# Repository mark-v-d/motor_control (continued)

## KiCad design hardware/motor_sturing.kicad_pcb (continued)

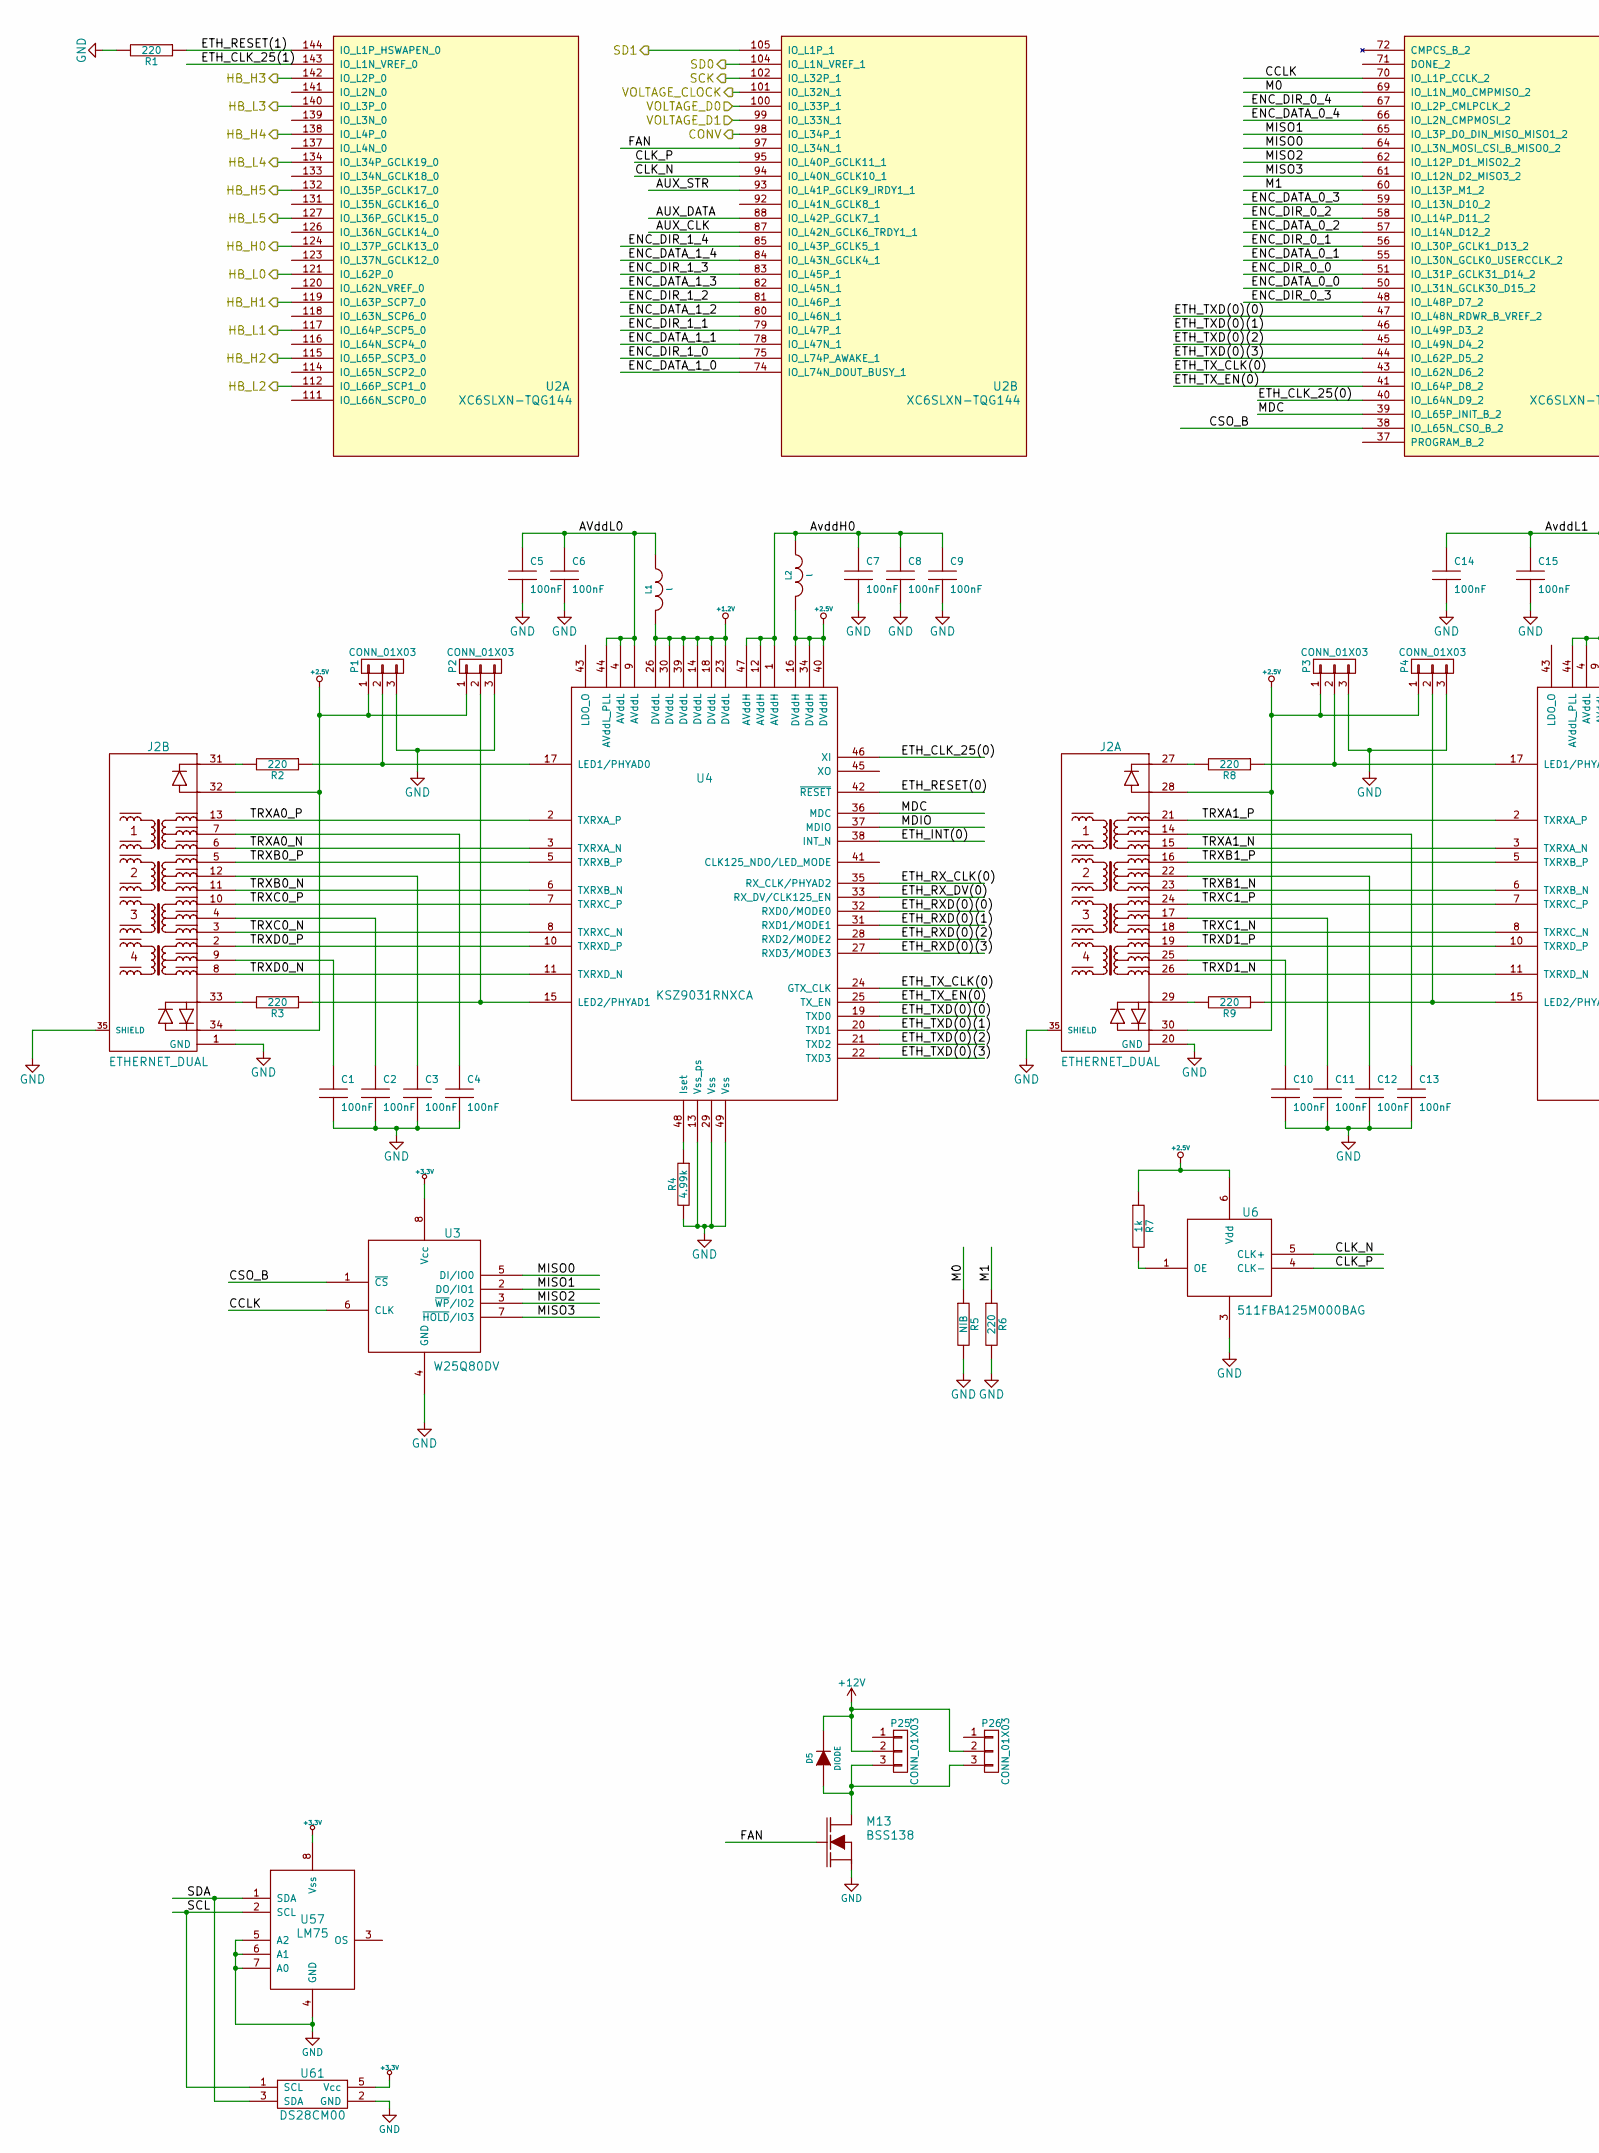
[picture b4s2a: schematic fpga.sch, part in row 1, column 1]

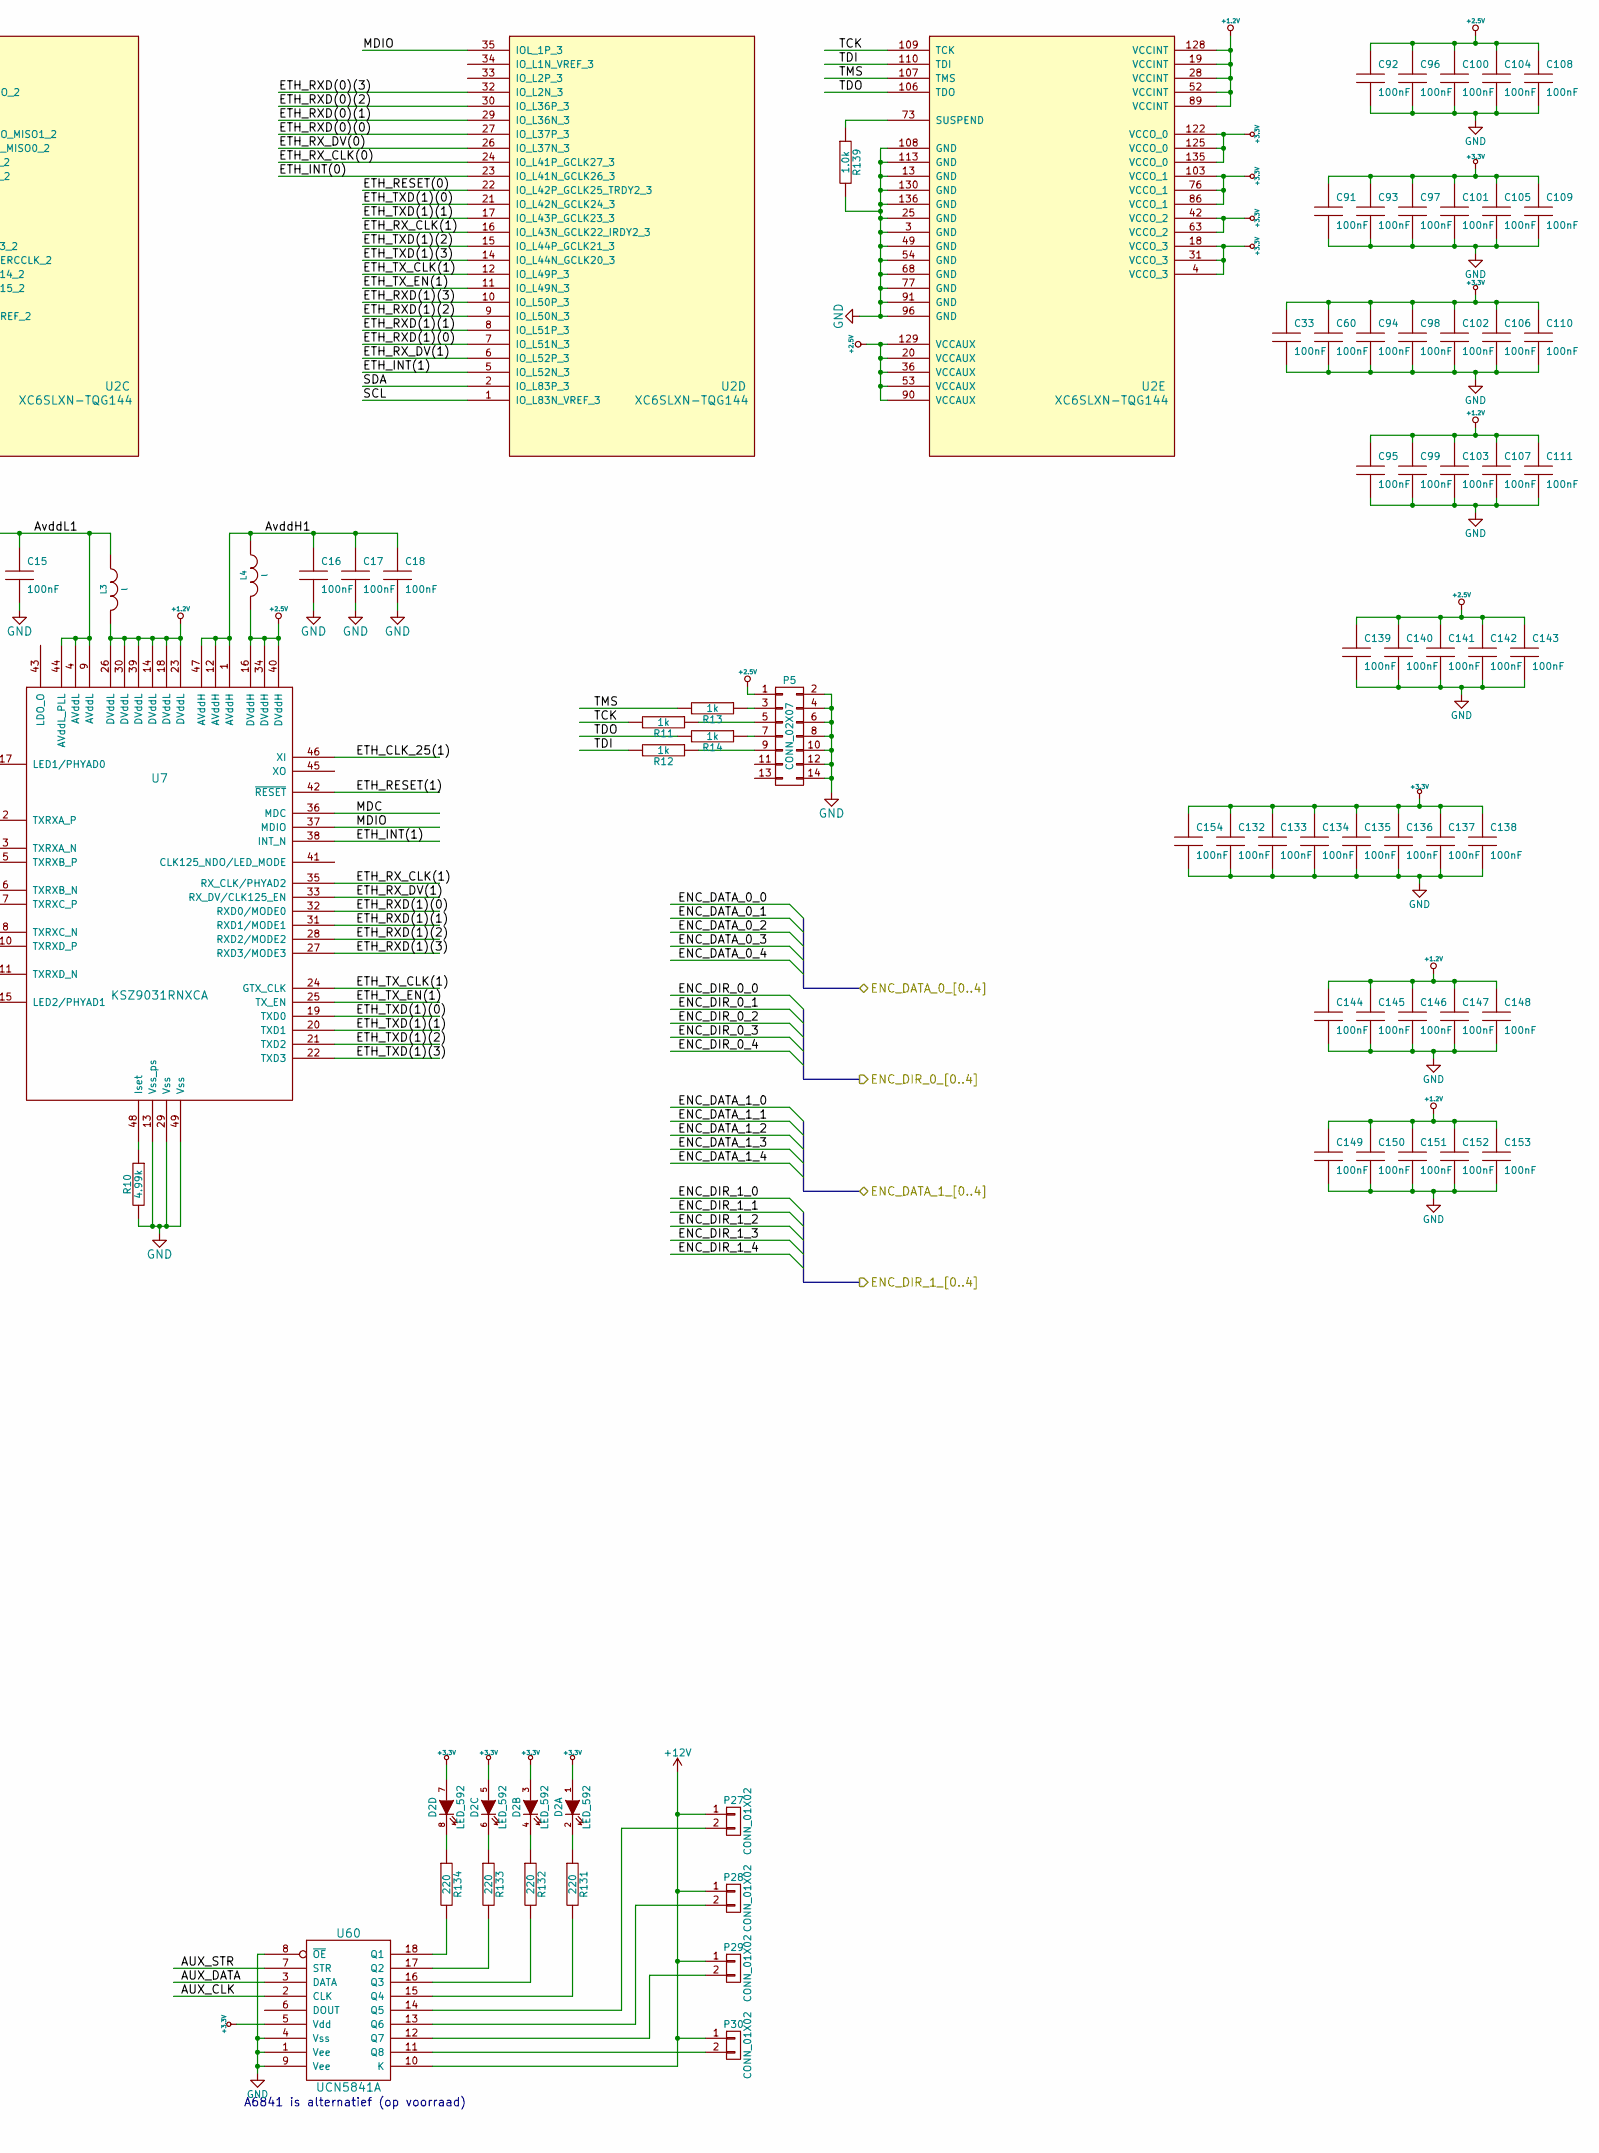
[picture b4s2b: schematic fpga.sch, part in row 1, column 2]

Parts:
C1, C2, C3, C4, C5, C6, C7, C8, C9, C10, C11, C12, C13, C14, C15, C16, C17, C18, C33, C60, C91, C92, C93, C94, C95, C96, C97, C98, C99, C100, C101, C102, C103, C104, C105, C106, C107, C108, C109, C110, C111, C132, C133, C134, C135, C136, C137, C138, C139, C140, C141, C142, C143, C144, C145, C146, C147, C148, C149, C150, C151, C152, C153, C154: 100nF; C0603
D2: LED_592; LED_592-3030-013F
D5: DIODE; SOD-323
J2: ETHERNET_DUAL; PartNr 0845-2R1T-E4; Digikey 380-1124-ND
L1, L2, L3, L4: l; L0805
M13: BSS138; SOT23_GSD
P1, P2, P3, P4: CONN_01X03; R0603_3
P5: CONN_02X07; header_2mm_7x2_smd
P25, P26: CONN_01X03; Pin_Header_Straight_1x03; PartNr 22-23-2031; Farnell 1462950
P27, P28, P29, P30: CONN_01X02; PINHEAD1-2
R1, R2, R3, R6, R8, R9, R131, R132, R133, R134: 220; R0603
R4, R10: 4.99k; R0603
R5: NIB; C0603
R7, R11, R12, R13, R14: 1k; R0603
R139: 1.0k; R0603
U2: XC6SLXN-TQG144; LQFP-144_20x20mm_Pitch0.5mm
U3: W25Q80DV; SOIC-8_3.9x4.9mm_Pitch1.27mm; Digikey W25Q80DVSNIG-ND
U4, U7: KSZ9031RNXCA; QFN-48-1EP_7x7mm_Pitch0.5mm; Digikey 576-4041-1-ND
U6: 511FBA125M000BAG; osc_5x7-6; Digikey 336-2637-ND
U57: LM75; SOIC-8_3.9x4.9mm_Pitch1.27mm
U60: UCN5841A; DIP-18_W7.62mm; Farnell 1202821
U61: DS28CM00; SOT23_5

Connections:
+1.2V: C95.1, C99.1, C103.1, C107.1, C111.1, C144.1, C145.1, C146.1, C147.1, C148.1, C149.1, C150.1, C151.1, C152.1, C153.1, L1.2, L3.2, U2.19 (VCCINT), U2.28 (VCCINT), U2.52 (VCCINT), U2.89 (VCCINT), U2.128 (VCCINT), U4.14 (DVddL), U4.18 (DVddL), U4.23 (DVddL), U4.26 (DVddL), U4.30 (DVddL), U4.39 (DVddL), U7.14 (DVddL), U7.18 (DVddL), U7.23 (DVddL), U7.26 (DVddL), U7.30 (DVddL), U7.39 (DVddL); also elsewhere on the board
+2.5V: C92.1, C96.1, C100.1, C104.1, C108.1, C139.1, C140.1, C141.1, C142.1, C143.1, J2.28, J2.30, J2.32, J2.34, L2.2, L4.2, P1.1, P2.1, P3.1, P4.1, P5.1, R7.1, U2.20 (VCCAUX), U2.36 (VCCAUX), U2.53 (VCCAUX), U2.90 (VCCAUX), U2.129 (VCCAUX), U4.16 (DVddH), U4.34 (DVddH), U4.40 (DVddH), U6.6 (Vdd), U7.16 (DVddH), U7.34 (DVddH), U7.40 (DVddH); also elsewhere on the board
+3.3V: C33.1, C60.1, C91.1, C93.1, C94.1, C97.1, C98.1, C101.1, C102.1, C105.1, C106.1, C109.1, C110.1, C132.1, C133.1, C134.1, C135.1, C136.1, C137.1, C138.1, C154.1, D2.1 (A), D2.3 (A), D2.5 (A), D2.7 (A), U2.4 (VCCO_3), U2.18 (VCCO_3), U2.31 (VCCO_3), U2.42 (VCCO_2), U2.63 (VCCO_2), U2.76 (VCCO_1), U2.86 (VCCO_1), U2.103 (VCCO_1), U2.122 (VCCO_0), U2.125 (VCCO_0), U2.135 (VCCO_0), U3.8 (Vcc), U57.8 (Vss), U60.5 (Vdd), U61.5 (Vcc); also elsewhere on the board
+12V: D5.C, P25.2, P26.2, P27.1, P28.1, P29.1, P30.1, U60.10 (K); also elsewhere on the board
/Drive_1/ENC_DATA0: U2.50 (IO_L31N_GCLK30_D15_2); also elsewhere on the board
/Drive_1/ENC_DATA1: U2.55 (IO_L30N_GCLK0_USERCCLK_2); also elsewhere on the board
/Drive_1/ENC_DATA2: U2.57 (IO_L14N_D12_2); also elsewhere on the board
/Drive_1/ENC_DATA3: U2.59 (IO_L13N_D10_2); also elsewhere on the board
/Drive_1/ENC_DATA4: U2.66 (IO_L2N_CMPMOSI_2); also elsewhere on the board
/Drive_1/ENC_DIR0: U2.51 (IO_L31P_GCLK31_D14_2); also elsewhere on the board
/Drive_1/ENC_DIR1: U2.56 (IO_L30P_GCLK1_D13_2); also elsewhere on the board
/Drive_1/ENC_DIR2: U2.58 (IO_L14P_D11_2); also elsewhere on the board
/Drive_1/ENC_DIR3: U2.48 (IO_L48P_D7_2); also elsewhere on the board
/Drive_1/ENC_DIR4: U2.67 (IO_L2P_CMLPCLK_2); also elsewhere on the board
/Drive_1/H0: U2.124 (IO_L37P_GCLK13_0); also elsewhere on the board
/Drive_1/H1: U2.119 (IO_L63P_SCP7_0); also elsewhere on the board
/Drive_1/H2: U2.115 (IO_L65P_SCP3_0); also elsewhere on the board
/Drive_1/VOLTAGE_CLOCK: U2.101 (IO_L32N_1); also elsewhere on the board
/Drive_2/ENC_DATA0: U2.74 (IO_L74N_DOUT_BUSY_1); also elsewhere on the board
/Drive_2/ENC_DATA1: U2.78 (IO_L47N_1); also elsewhere on the board
/Drive_2/ENC_DATA2: U2.80 (IO_L46N_1); also elsewhere on the board
/Drive_2/ENC_DATA3: U2.82 (IO_L45N_1); also elsewhere on the board
/Drive_2/ENC_DATA4: U2.84 (IO_L43N_GCLK4_1); also elsewhere on the board
/Drive_2/ENC_DIR0: U2.75 (IO_L74P_AWAKE_1); also elsewhere on the board
/Drive_2/ENC_DIR1: U2.79 (IO_L47P_1); also elsewhere on the board
/Drive_2/ENC_DIR2: U2.81 (IO_L46P_1); also elsewhere on the board
/Drive_2/ENC_DIR3: U2.83 (IO_L45P_1); also elsewhere on the board
/Drive_2/ENC_DIR4: U2.85 (IO_L43P_GCLK5_1); also elsewhere on the board
/Drive_2/H0: U2.142 (IO_L2P_0); also elsewhere on the board
/Drive_2/H1: U2.138 (IO_L4P_0); also elsewhere on the board
/Drive_2/H2: U2.132 (IO_L35P_GCLK17_0); also elsewhere on the board
/FPGA/AUX_CLK: U2.87 (IO_L42N_GCLK6_TRDY1_1), U60.2 (CLK)
/FPGA/AUX_DATA: U2.88 (IO_L42P_GCLK7_1), U60.3 (DATA)
/FPGA/AUX_STR: U2.93 (IO_L41P_GCLK9_IRDY1_1), U60.7 (STR)
/FPGA/AVddL0: C5.1, C6.1, L1.1, U4.4 (AVddL), U4.9 (AVddL), U4.44 (AVddL_PLL)
/FPGA/AvddH0: C7.1, C8.1, C9.1, L2.1, U4.1 (AVddH), U4.12 (AVddH), U4.47 (AVddH)
/FPGA/AvddH1: C16.1, C17.1, C18.1, L4.1, U7.1 (AVddH), U7.12 (AVddH), U7.47 (AVddH)
/FPGA/AvddL1: C14.1, C15.1, L3.1, U7.4 (AVddL), U7.9 (AVddL), U7.44 (AVddL_PLL)
/FPGA/CCLK: U2.70 (IO_L1P_CCLK_2), U3.6 (CLK)
/FPGA/CLK_N: U2.94 (IO_L40N_GCLK10_1), U6.5 (CLK+)
/FPGA/CLK_P: U2.95 (IO_L40P_GCLK11_1), U6.4 (CLK-)
/FPGA/CONV: U2.98 (IO_L34P_1); also elsewhere on the board
/FPGA/CSO_B: U2.38 (IO_L65N_CSO_B_2), U3.1 (~CS)
/FPGA/ETH_CLK_25(0): U2.40 (IO_L64N_D9_2), U4.46 (XI)
/FPGA/ETH_CLK_25(1): U2.143 (IO_L1N_VREF_0), U7.46 (XI)
/FPGA/ETH_INT(0): U2.23 (IO_L41N_GCLK26_3), U4.38 (INT_N)
/FPGA/ETH_INT(1): U2.5 (IO_L52N_3), U7.38 (INT_N)
/FPGA/ETH_RESET(0): U2.22 (IO_L42P_GCLK25_TRDY2_3), U4.42 (~RESET)
/FPGA/ETH_RESET(1): R1.1, U2.144 (IO_L1P_HSWAPEN_0), U7.42 (~RESET)
/FPGA/ETH_RXD(0)(0): U2.27 (IO_L37P_3), U4.32 (RXD0/MODE0)
/FPGA/ETH_RXD(0)(1): U2.29 (IO_L36N_3), U4.31 (RXD1/MODE1)
/FPGA/ETH_RXD(0)(2): U2.30 (IO_L36P_3), U4.28 (RXD2/MODE2)
/FPGA/ETH_RXD(0)(3): U2.32 (IO_L2N_3), U4.27 (RXD3/MODE3)
/FPGA/ETH_RXD(1)(0): U2.7 (IO_L51N_3), U7.32 (RXD0/MODE0)
/FPGA/ETH_RXD(1)(1): U2.8 (IO_L51P_3), U7.31 (RXD1/MODE1)
/FPGA/ETH_RXD(1)(2): U2.9 (IO_L50N_3), U7.28 (RXD2/MODE2)
/FPGA/ETH_RXD(1)(3): U2.10 (IO_L50P_3), U7.27 (RXD3/MODE3)
/FPGA/ETH_RX_CLK(0): U2.24 (IO_L41P_GCLK27_3), U4.35 (RX_CLK/PHYAD2)
/FPGA/ETH_RX_CLK(1): U2.16 (IO_L43N_GCLK22_IRDY2_3), U7.35 (RX_CLK/PHYAD2)
/FPGA/ETH_RX_DV(0): U2.26 (IO_L37N_3), U4.33 (RX_DV/CLK125_EN)
/FPGA/ETH_RX_DV(1): U2.6 (IO_L52P_3), U7.33 (RX_DV/CLK125_EN)
/FPGA/ETH_TXD(0)(0): U2.47 (IO_L48N_RDWR_B_VREF_2), U4.19 (TXD0)
/FPGA/ETH_TXD(0)(1): U2.46 (IO_L49P_D3_2), U4.20 (TXD1)
/FPGA/ETH_TXD(0)(2): U2.45 (IO_L49N_D4_2), U4.21 (TXD2)
/FPGA/ETH_TXD(0)(3): U2.44 (IO_L62P_D5_2), U4.22 (TXD3)
/FPGA/ETH_TXD(1)(0): U2.21 (IO_L42N_GCLK24_3), U7.19 (TXD0)
/FPGA/ETH_TXD(1)(1): U2.17 (IO_L43P_GCLK23_3), U7.20 (TXD1)
/FPGA/ETH_TXD(1)(2): U2.15 (IO_L44P_GCLK21_3), U7.21 (TXD2)
/FPGA/ETH_TXD(1)(3): U2.14 (IO_L44N_GCLK20_3), U7.22 (TXD3)
/FPGA/ETH_TX_CLK(0): U2.43 (IO_L62N_D6_2), U4.24 (GTX_CLK)
/FPGA/ETH_TX_CLK(1): U2.12 (IO_L49P_3), U7.24 (GTX_CLK)
/FPGA/ETH_TX_EN(0): U2.41 (IO_L64P_D8_2), U4.25 (TX_EN)
/FPGA/ETH_TX_EN(1): U2.11 (IO_L49N_3), U7.25 (TX_EN)
/FPGA/FAN: M13.G, U2.97 (IO_L34N_1)
/FPGA/HB_L0: U2.121 (IO_L62P_0); also elsewhere on the board
/FPGA/HB_L1: U2.117 (IO_L64P_SCP5_0); also elsewhere on the board
/FPGA/HB_L2: U2.112 (IO_L66P_SCP1_0); also elsewhere on the board
/FPGA/HB_L3: U2.140 (IO_L3P_0); also elsewhere on the board
/FPGA/HB_L4: U2.134 (IO_L34P_GCLK19_0); also elsewhere on the board
/FPGA/HB_L5: U2.127 (IO_L36P_GCLK15_0); also elsewhere on the board
/FPGA/M0: R5.1, U2.69 (IO_L1N_M0_CMPMISO_2)
/FPGA/M1: R6.1, U2.60 (IO_L13P_M1_2)
/FPGA/MDC: U2.39 (IO_L65P_INIT_B_2), U4.36 (MDC), U7.36 (MDC)
/FPGA/MDIO: U2.35 (IOL_1P_3), U4.37 (MDIO), U7.37 (MDIO)
/FPGA/MISO0: U2.64 (IO_L3N_MOSI_CSI_B_MISO0_2), U3.5 (DI/IO0)
/FPGA/MISO1: U2.65 (IO_L3P_D0_DIN_MISO_MISO1_2), U3.2 (DO/IO1)
/FPGA/MISO2: U2.62 (IO_L12P_D1_MISO2_2), U3.3 (~WP~/IO2)
/FPGA/MISO3: U2.61 (IO_L12N_D2_MISO3_2), U3.7 (~HOLD~/IO3)
/FPGA/SCK: U2.102 (IO_L32P_1); also elsewhere on the board
/FPGA/SCL: U2.1 (IO_L83N_VREF_3), U57.2 (SCL), U61.1 (SCL)
/FPGA/SD0: U2.104 (IO_L1N_VREF_1); also elsewhere on the board
/FPGA/SD1: U2.105 (IO_L1P_1); also elsewhere on the board
/FPGA/SDA: U2.2 (IO_L83P_3), U57.1 (SDA), U61.3 (SDA)
/FPGA/TCK: R11.2, U2.109 (TCK)
/FPGA/TDI: R12.2, U2.110 (TDI)
/FPGA/TDO: R14.2, U2.106 (TDO)
/FPGA/TMS: R13.2, U2.107 (TMS)
/FPGA/TRXA0_N: J2.6, U4.3 (TXRXA_N)
/FPGA/TRXA0_P: J2.13, U4.2 (TXRXA_P)
/FPGA/TRXA1_N: J2.15, U7.3 (TXRXA_N)
/FPGA/TRXA1_P: J2.21, U7.2 (TXRXA_P)
/FPGA/TRXB0_N: J2.11, U4.6 (TXRXB_N)
/FPGA/TRXB0_P: J2.5, U4.5 (TXRXB_P)
/FPGA/TRXB1_N: J2.23, U7.6 (TXRXB_N)
/FPGA/TRXB1_P: J2.16, U7.5 (TXRXB_P)
/FPGA/TRXC0_N: J2.3, U4.8 (TXRXC_N)
/FPGA/TRXC0_P: J2.10, U4.7 (TXRXC_P)
/FPGA/TRXC1_N: J2.18, U7.8 (TXRXC_N)
/FPGA/TRXC1_P: J2.24, U7.7 (TXRXC_P)
/FPGA/TRXD0_N: J2.8, U4.11 (TXRXD_N)
/FPGA/TRXD0_P: J2.2, U4.10 (TXRXD_P)
/FPGA/TRXD1_N: J2.26, U7.11 (TXRXD_N)
/FPGA/TRXD1_P: J2.19, U7.10 (TXRXD_P)
/FPGA/VOLTAGE_D0: U2.100 (IO_L33P_1); also elsewhere on the board
/FPGA/VOLTAGE_D1: U2.99 (IO_L33N_1); also elsewhere on the board
GND: C1.2, C2.2, C3.2, C4.2, C5.2, C6.2, C7.2, C8.2, C9.2, C10.2, C11.2, C12.2, C13.2, C14.2, C15.2, C16.2, C17.2, C18.2, C33.2, C60.2, C91.2, C92.2, C93.2, C94.2, C95.2, C96.2, C97.2, C98.2, C99.2, C100.2, C101.2, C102.2, C103.2, C104.2, C105.2, C106.2, C107.2, C108.2, C109.2, C110.2, C111.2, C132.2, C133.2, C134.2, C135.2, C136.2, C137.2, C138.2, C139.2, C140.2, C141.2, C142.2, C143.2, C144.2, C145.2, C146.2, C147.2, C148.2, C149.2, C150.2, C151.2, C152.2, C153.2, C154.2, J2.1 (GND), J2.20 (GND), J2.35 (SHIELD), M13.S, P1.3, P2.3, P3.3, P4.3, P5.2, P5.4, P5.6, P5.8, P5.10, P5.12, P5.14, R1.2, R4.2, R5.2, R6.2, R10.2, R139.2, U2.3 (GND), U2.13 (GND), U2.25 (GND), U2.49 (GND), U2.54 (GND), U2.68 (GND), U2.77 (GND), U2.91 (GND), U2.96 (GND), U2.108 (GND), U2.113 (GND), U2.130 (GND), U2.136 (GND), U3.4 (GND), U4.13 (Vss_ps), U4.29 (Vss), U4.49 (Vss), U6.3, U7.13 (Vss_ps), U7.29 (Vss), U7.49 (Vss), U57.4 (GND), U57.5 (A2), U57.6 (A1), U57.7 (A0), U60.1 (Vee), U60.4 (Vss), U60.8 (~OE), U60.9 (Vee), U61.2 (GND); also elsewhere on the board
unnamed: C1.1, J2.9
unnamed: C2.1, J2.4
unnamed: C3.1, J2.12
unnamed: C4.1, J2.7
unnamed: C10.1, J2.25
unnamed: C11.1, J2.17
unnamed: C12.1, J2.22
unnamed: C13.1, J2.14
unnamed: D2.2 (K), R131.1
unnamed: D2.4 (K), R132.1
unnamed: D2.6 (K), R133.1
unnamed: D2.8 (K), R134.1
unnamed: D5.A, M13.D, P25.3, P26.3
unnamed: J2.27, R8.2
unnamed: J2.29, R9.2
unnamed: J2.31, R2.2
unnamed: J2.33, R3.2
unnamed: P1.2, R2.1, U4.17 (LED1/PHYAD0)
unnamed: P2.2, R3.1, U4.15 (LED2/PHYAD1)
unnamed: P3.2, R8.1, U7.17 (LED1/PHYAD0)
unnamed: P4.2, R9.1, U7.15 (LED2/PHYAD1)
unnamed: P5.3, R13.1
unnamed: P5.5, R11.1
unnamed: P5.7, R14.1
unnamed: P5.9, R12.1
unnamed: P27.2, U60.14 (Q5)
unnamed: P28.2, U60.13 (Q6)
unnamed: P29.2, U60.12 (Q7)
unnamed: P30.2, U60.11 (Q8)
unnamed: R4.1, U4.48 (Iset)
unnamed: R7.2, U6.1 (OE)
unnamed: R10.1, U7.48 (Iset)
unnamed: R131.2, U60.15 (Q4)
unnamed: R132.2, U60.16 (Q3)
unnamed: R133.2, U60.17 (Q2)
unnamed: R134.2, U60.18 (Q1)
unnamed: R139.1, U2.73 (SUSPEND)

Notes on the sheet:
A6841 is alternatief (op voorraad)
